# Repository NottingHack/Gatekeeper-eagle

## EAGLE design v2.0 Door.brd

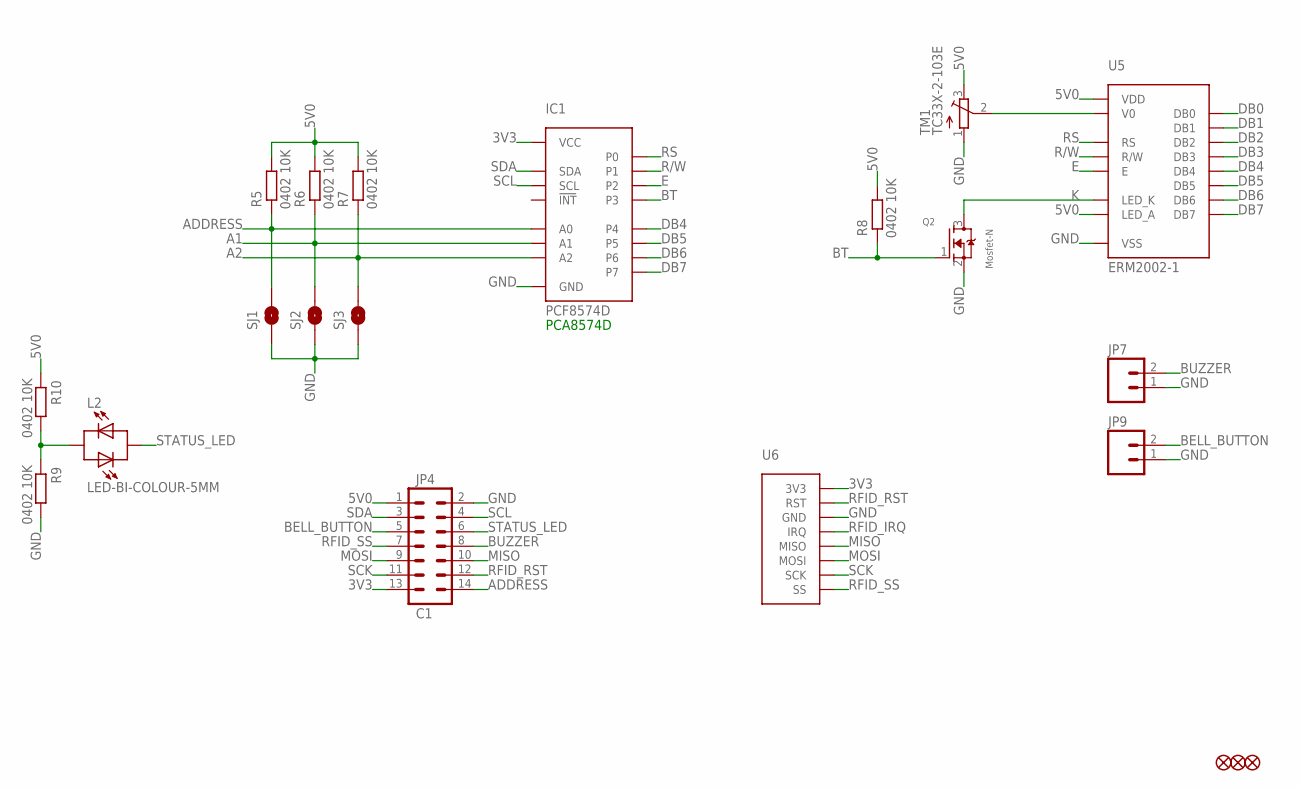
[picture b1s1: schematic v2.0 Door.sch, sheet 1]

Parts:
IC1: PCF8574D; SO16
JP1, JP2, JP3: FIDUCIAL1X2.5-STOP; FIDUCIAL-1X2.5-STOP
JP4: C1; 2X7-SHROUDED_LOCK
JP7, JP9: M02POLAR_LOCK; MOLEX-1X2_LOCK
L2: LED-BI-COLOUR-5MM; LED5MM
Q2: Mosfet-N; SOT23-3
R5, R6, R7, R8, R9, R10: 0402 10K; R0402-SMALLER
SJ1, SJ2, SJ3: SOLDERJUMPERNO; SJ_2S-NO
TM1: TC33X-2-103E; TC33X
U5: ERM2002-1; ERM2002-1-GATEKEEPER
U6: RFID-RC522-GATEKEEPER

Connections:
3V3: IC1.16 (VCC), JP4.13, U6.8 (3V3)
5V0: JP4.1, R5.2, R6.2, R7.2, R8.2, R10.1, TM1.3 (E), U5.2 (VDD), U5.15 (LED_A)
A1: IC1.2 (A1), R6.1, SJ2.2
A2: IC1.3 (A2), R7.1, SJ3.2
ADDRESS: IC1.1 (A0), JP4.14, R5.1, SJ1.2
BELL_BUTTON: JP4.5, JP9.2
BT: IC1.7 (P3), Q2.1 (G), R8.1
BUZZER: JP4.8, JP7.2
DB0: U5.7 (DB0)
DB1: U5.8 (DB1)
DB2: U5.9 (DB2)
DB3: U5.10 (DB3)
DB4: IC1.9 (P4), U5.11 (DB4)
DB5: IC1.10 (P5), U5.12 (DB5)
DB6: IC1.11 (P6), U5.13 (DB6)
DB7: IC1.12 (P7), U5.14 (DB7)
E: IC1.6 (P2), U5.6 (E)
GND: IC1.8 (GND), JP4.2, JP7.1, JP9.1, Q2.2 (S), R9.2, SJ1.1, SJ2.1, SJ3.1, TM1.1 (A), U5.1 (VSS), U6.6 (GND)
K: Q2.3 (D), U5.16 (LED_K)
MISO: JP4.10, U6.4 (MISO)
MOSI: JP4.9, U6.3 (MOSI)
unnamed: TM1.2 (S), U5.3 (V0)
unnamed: L2.A (1), R9.1, R10.2
R/W: IC1.5 (P1), U5.5 (R/W)
RFID_IRQ: U6.5 (IRQ)
RFID_RST: JP4.12, U6.7 (RST)
RFID_SS: JP4.7, U6.1 (SS)
RS: IC1.4 (P0), U5.4 (RS)
SCK: JP4.11, U6.2 (SCK)
SCL: IC1.14 (SCL), JP4.4
SDA: IC1.15 (SDA), JP4.3
STATUS_LED: JP4.6, L2.K (2)

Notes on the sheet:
PCA8574D

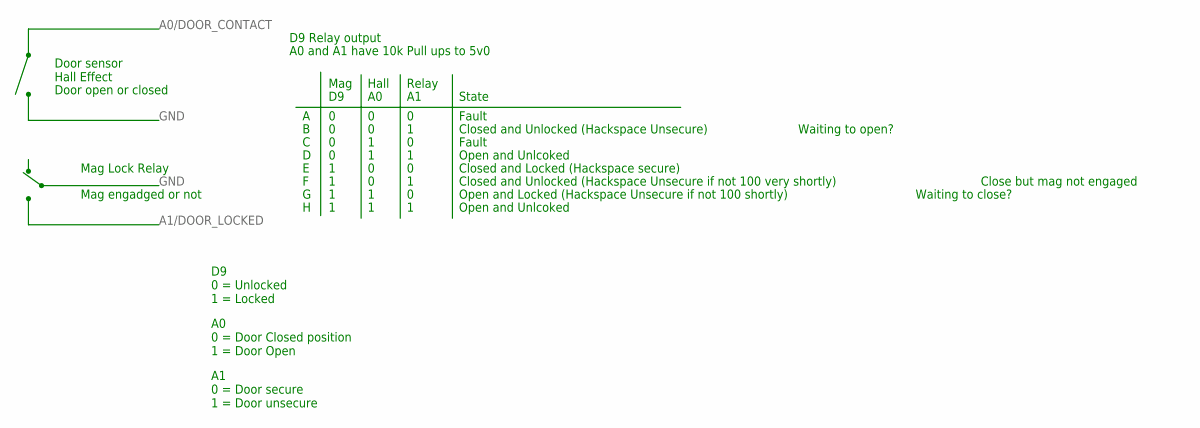
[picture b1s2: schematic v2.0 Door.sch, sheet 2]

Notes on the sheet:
Door sensor Hall Effect
Mag Lock Relay
A0 and A1 have 10k Pull ups to 5v0
Hall
Relay
State
Closed and Locked (Hackspace secure)
Closed and Unlocked (Hackspace Unsecure)
Open and Locked (Hackspace Unsecure if not 100 shortly)
Open and Unlcoked
Mag
Door open or closed
Mag engadged or not
D9 0 = Unlocked 1 = Locked
A0 0 = Door Closed position 1 = Door Open
A1 0 = Door secure 1 = Door unsecure
Fault
Waiting to open?
D9 Relay output
Closed and Unlocked (Hackspace Unsecure if not 100 very shortly)
Waiting to close?
A B C D E F G H
Close but mag not engaged

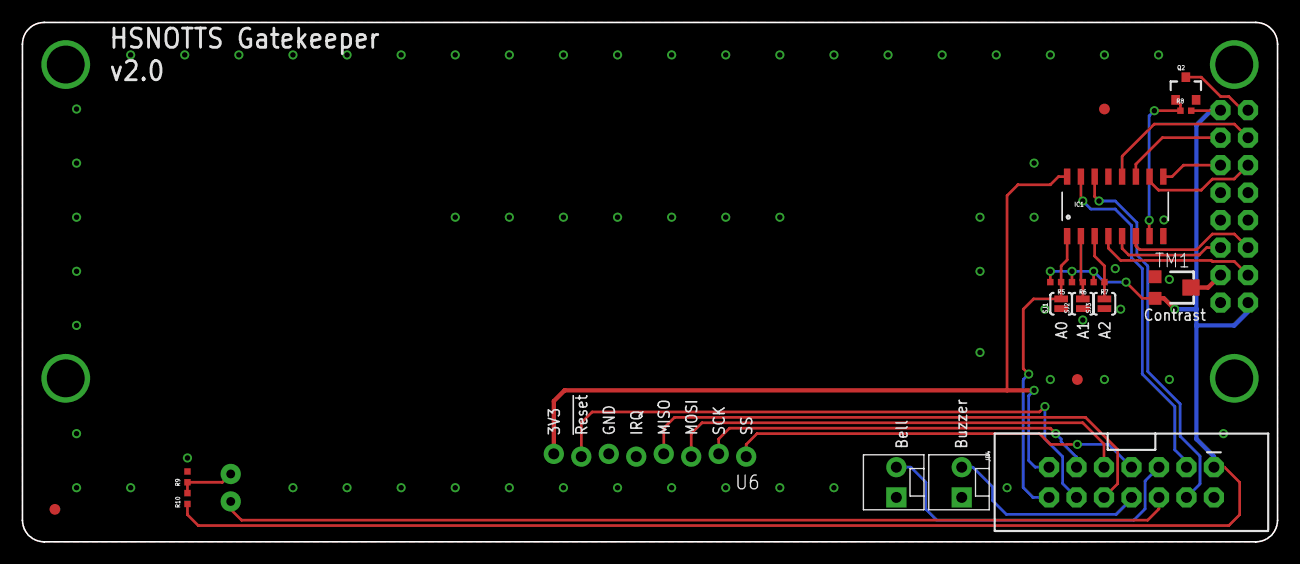
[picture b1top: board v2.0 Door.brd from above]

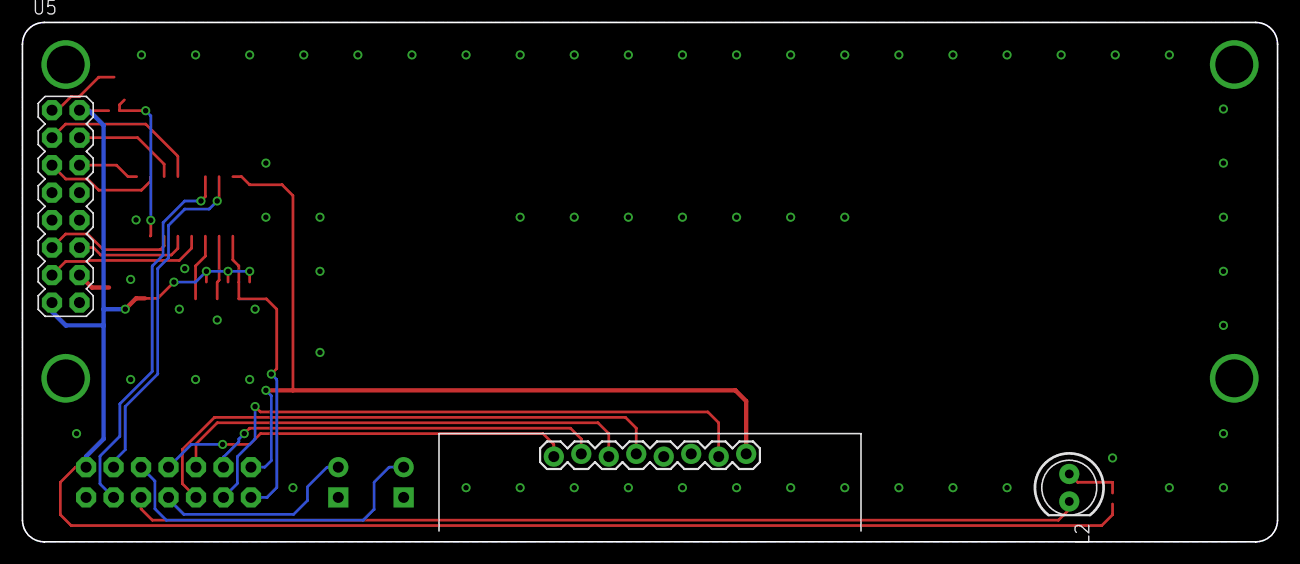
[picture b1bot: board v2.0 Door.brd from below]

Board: 2 copper layers, 116.0 x 48.0 mm, 21 parts (2 on the bottom side), 27 nets.

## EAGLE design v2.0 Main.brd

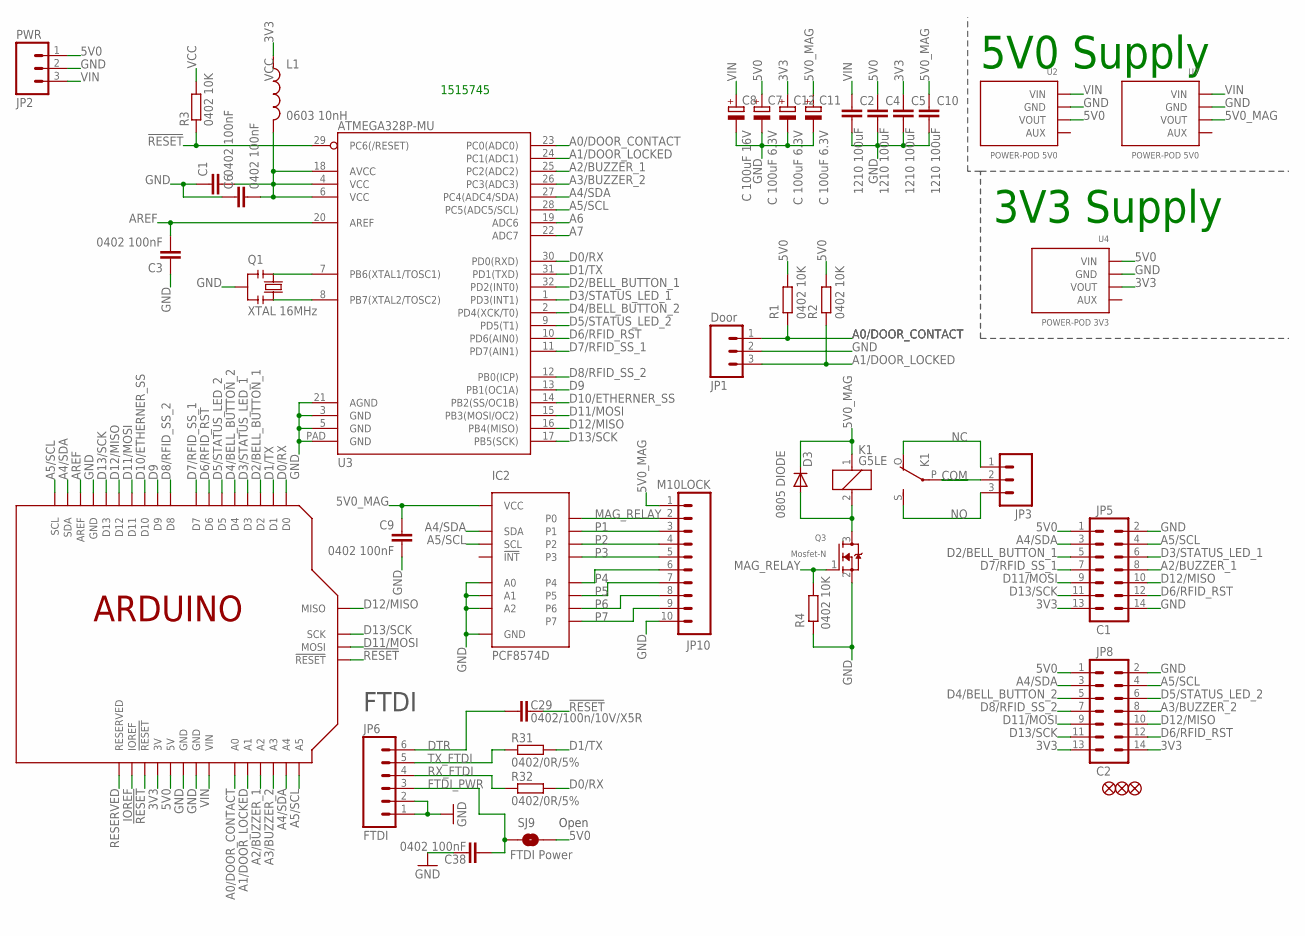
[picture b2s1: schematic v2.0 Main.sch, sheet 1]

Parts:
C1, C3, C6, C9, C38: 0402 100nF; C0402-SMALLER
C2, C4, C5, C10: 1210 100uF; C1210
C7, C11, C12: C 100uF 6.3V; PANASONIC_C
C8: C 100uF 16V; PANASONIC_C
C29: 0402/100n/10V/X5R; C0402-ARDUINO-ROUND
D3: 0805 DIODE; 0805-DIODE
IC2: PCF8574D; SO16
JP1: Door; SCREWTERMINAL-5MM-3
JP2: PWR; SCREWTERMINAL-5MM-3
JP3: M03-SCREW-5MM; SCREWTERMINAL-5MM-3
JP4, JP7, JP9: FIDUCIAL1X2.5-STOP; FIDUCIAL-1X2.5-STOP
JP5: C1; 2X7-SHROUDED_LOCK
JP6: FTDI; 1X06
JP8: C2; 2X7-SHROUDED_LOCK
JP10: M10LOCK; 1X10_LOCK
K1: G5LE; G5LE-NOSTOP-SMALL
L1: 0603 10nH; C0603K-SMALL
Q1: XTAL 16MHz; RESONATOR
Q3: Mosfet-N; SOT23-3
R1, R2, R3, R4: 0402 10K; R0402-SMALLER
R31, R32: 0402/0R/5%; R0402-ARDUINO-ROUND
SJ9: FTDI Power; SJ_2S-TRACE
U1: ARDUINOSPI-REFRENCE; ARDUINOR3-LWKTXT-REF-SPI
U2, U7: POWER-POD 5V0; POWER-POD-LANDING
U3: ATMEGA328P-MU; MLF32-SHORT-CREAM
U4: POWER-POD 3V3; POWER-POD-LANDING

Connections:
3V3: C5.1, C12.+, JP5.13, JP8.13, JP8.14, L1.1, U1.3V, U4.3 (VOUT)
5V0: C4.1, C7.+, JP2.1, JP5.1, JP8.1, R1.2, R2.2, SJ9.2, U1.5V, U1.5V@ISP (5V), U2.3 (VOUT), U4.1 (VIN)
5V0_MAG: C9.1, C10.1, C11.+, D3.C, IC2.16 (VCC), JP10.1, K1.1, U7.3 (VOUT)
!RESET: C29.1, R3.1, U1.!RESET, U1.!RESET@ISP (!RESET), U3.29 (PC6(/RESET))
A0/DOOR_CONTACT: JP1.1, R1.1, U1.A0, U3.23 (PC0(ADC0))
A1/DOOR_LOCKED: JP1.3, R2.1, U1.A1, U3.24 (PC1(ADC1))
A2/BUZZER_1: JP5.8, U1.A2, U3.25 (PC2(ADC2))
A3/BUZZER_2: JP8.8, U1.A3, U3.26 (PC3(ADC3))
A4/SDA: IC2.15 (SDA), JP5.3, JP8.3, U1.A4, U1.SDA, U3.27 (PC4(ADC4/SDA))
A5/SCL: IC2.14 (SCL), JP5.4, JP8.4, U1.A5, U1.SCL, U3.28 (PC5(ADC5/SCL))
A6: U3.19 (ADC6)
A7: U3.22 (ADC7)
AREF: C3.2, U1.AREF, U3.20 (AREF)
COM: JP3.2, K1.P
D0/RX: R32.2, U1.D0, U3.30 (PD0(RXD))
D1/TX: R31.2, U1.D1, U3.31 (PD1(TXD))
D2/BELL_BUTTON_1: JP5.5, U1.D2, U3.32 (PD2(INT0))
D3/STATUS_LED_1: JP5.6, U1.D3, U3.1 (PD3(INT1))
D4/BELL_BUTTON_2: JP8.5, U1.D4, U3.2 (PD4(XCK/T0))
D5/STATUS_LED_2: JP8.6, U1.D5, U3.9 (PD5(T1))
D6/RFID_RST: JP5.12, JP8.12, U1.D6, U3.10 (PD6(AIN0))
D7/RFID_SS_1: JP5.7, U1.D7, U3.11 (PD7(AIN1))
D8/RFID_SS_2: JP8.7, U1.D8, U3.12 (PB0(ICP))
D9: U1.D9, U3.13 (PB1(OC1A))
D10/ETHERNER_SS: U1.D10, U3.14 (PB2(SS/OC1B))
D11/MOSI: JP5.9, JP8.9, U1.D11, U1.MOSI, U3.15 (PB3(MOSI/OC2))
D12/MISO: JP5.10, JP8.10, U1.D12, U1.MISO, U3.16 (PB4(MISO))
D13/SCK: JP5.11, JP8.11, U1.D13, U1.SCK, U3.17 (PB5(SCK))
DTR: C29.2, JP6.6
FTDI_PWR: C38.2, JP6.3, SJ9.1
GND: C1.1, C2.2, C3.1, C4.2, C5.2, C6.1, C7.-, C8.-, C9.2, C10.2, C11.-, C12.-, C38.1, IC2.1 (A0), IC2.2 (A1), IC2.3 (A2), IC2.8 (GND), JP1.2, JP2.2, JP5.2, JP5.14, JP6.1, JP6.2, JP8.2, JP10.10, Q1.2, Q3.2 (S), R4.1, U1.GND@1 (GND), U1.GND@2 (GND), U1.GND@3 (GND), U1.GND@ISP (GND), U2.2 (GND), U3.3 (GND), U3.5 (GND), U3.21 (AGND), U3.PAD (GND), U4.2 (GND), U7.2 (GND)
IOREF: U1.IOREF
MAG_RELAY: IC2.4 (P0), JP10.2, Q3.1 (G), R4.2
unnamed: D3.A, K1.2, Q3.3 (D)
unnamed: Q1.1, U3.7 (PB6(XTAL1/TOSC1))
unnamed: Q1.3, U3.8 (PB7(XTAL2/TOSC2))
NC: JP3.1, K1.O
NO: JP3.3, K1.S
P1: IC2.5 (P1), JP10.3
P2: IC2.6 (P2), JP10.4
P3: IC2.7 (P3), JP10.5
P4: IC2.9 (P4), JP10.6
P5: IC2.10 (P5), JP10.7
P6: IC2.11 (P6), JP10.8
P7: IC2.12 (P7), JP10.9
RESERVED: U1.RESERVED
RX_FTDI: JP6.4, R32.1
TX_FTDI: JP6.5, R31.1
VCC: C1.2, C6.2, L1.2, R3.2, U3.4 (VCC), U3.6 (VCC), U3.18 (AVCC)
VIN: C2.1, C8.+, JP2.3, U1.VIN, U2.1 (VIN), U7.1 (VIN)

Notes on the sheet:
FTDI
Open
1515745
5V0 Supply
3V3 Supply

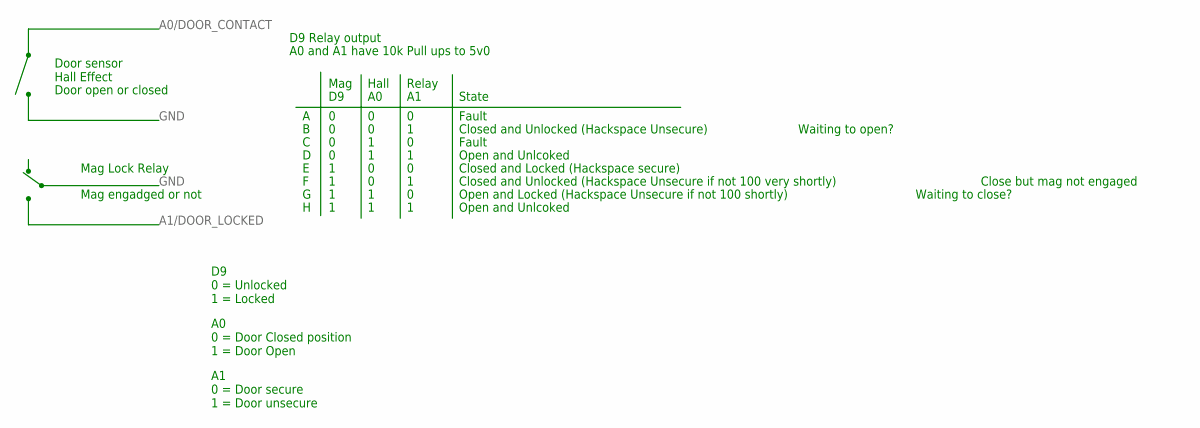
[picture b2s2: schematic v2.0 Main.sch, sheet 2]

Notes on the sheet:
Door sensor Hall Effect
Mag Lock Relay
A0 and A1 have 10k Pull ups to 5v0
Hall
Relay
State
Closed and Locked (Hackspace secure)
Closed and Unlocked (Hackspace Unsecure)
Open and Locked (Hackspace Unsecure if not 100 shortly)
Open and Unlcoked
Mag
Door open or closed
Mag engadged or not
D9 0 = Unlocked 1 = Locked
A0 0 = Door Closed position 1 = Door Open
A1 0 = Door secure 1 = Door unsecure
Fault
Waiting to open?
D9 Relay output
Closed and Unlocked (Hackspace Unsecure if not 100 very shortly)
Waiting to close?
A B C D E F G H
Close but mag not engaged

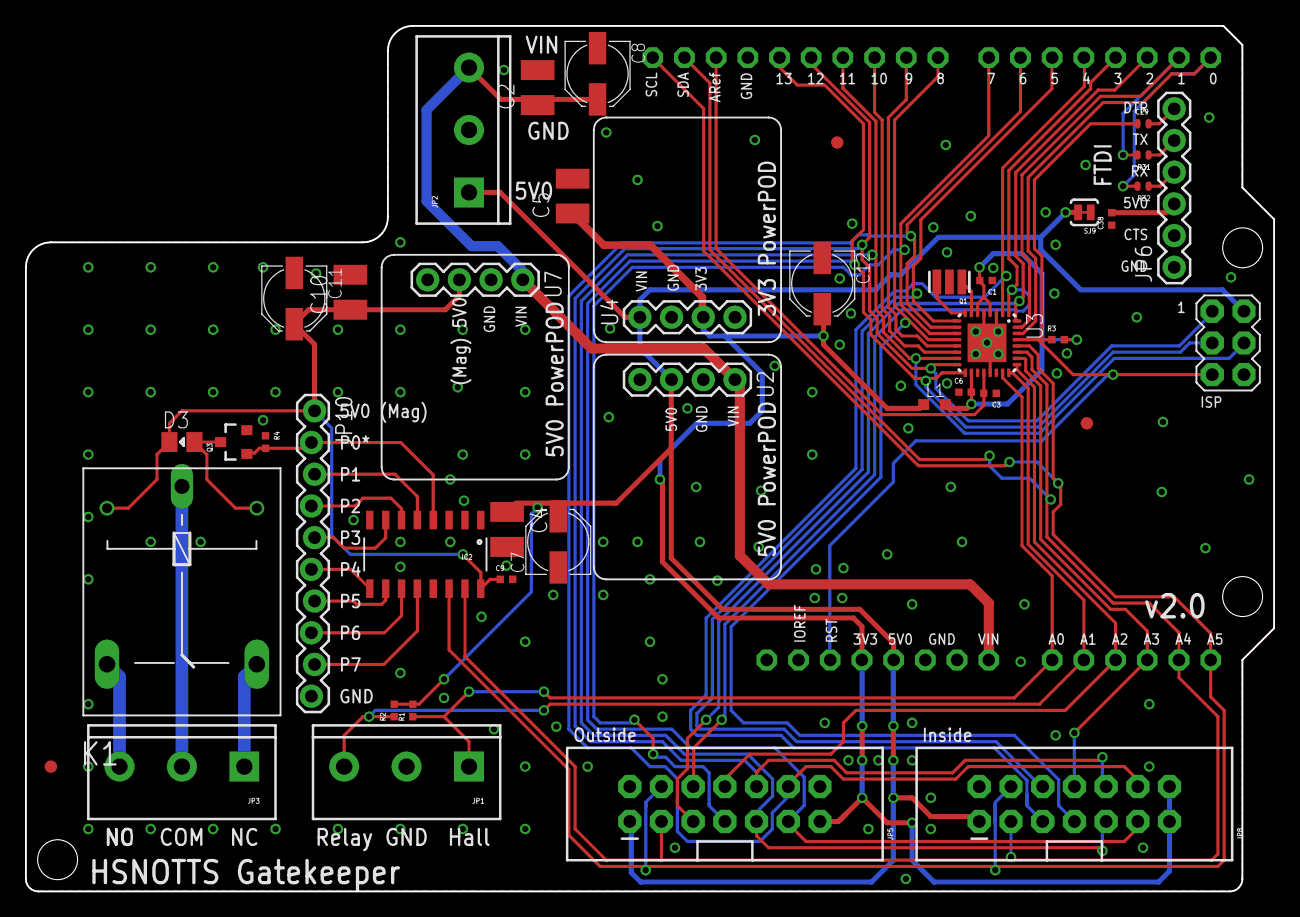
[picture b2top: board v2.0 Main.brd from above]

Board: 2 copper layers, 100.0 x 69.3 mm, 42 parts (0 on the bottom side), 46 nets.

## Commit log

2017-01-29 Tweaks and berbers
2017-01-29 Schematic PDF’s
2017-02-01 Update connectors
2018-08-29 Add the Fusion 360 archive and exported dxfs for the laser cut enclosure.
